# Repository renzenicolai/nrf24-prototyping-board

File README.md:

# nrf24-prototyping-board
Old project, uploaded just for you :-)

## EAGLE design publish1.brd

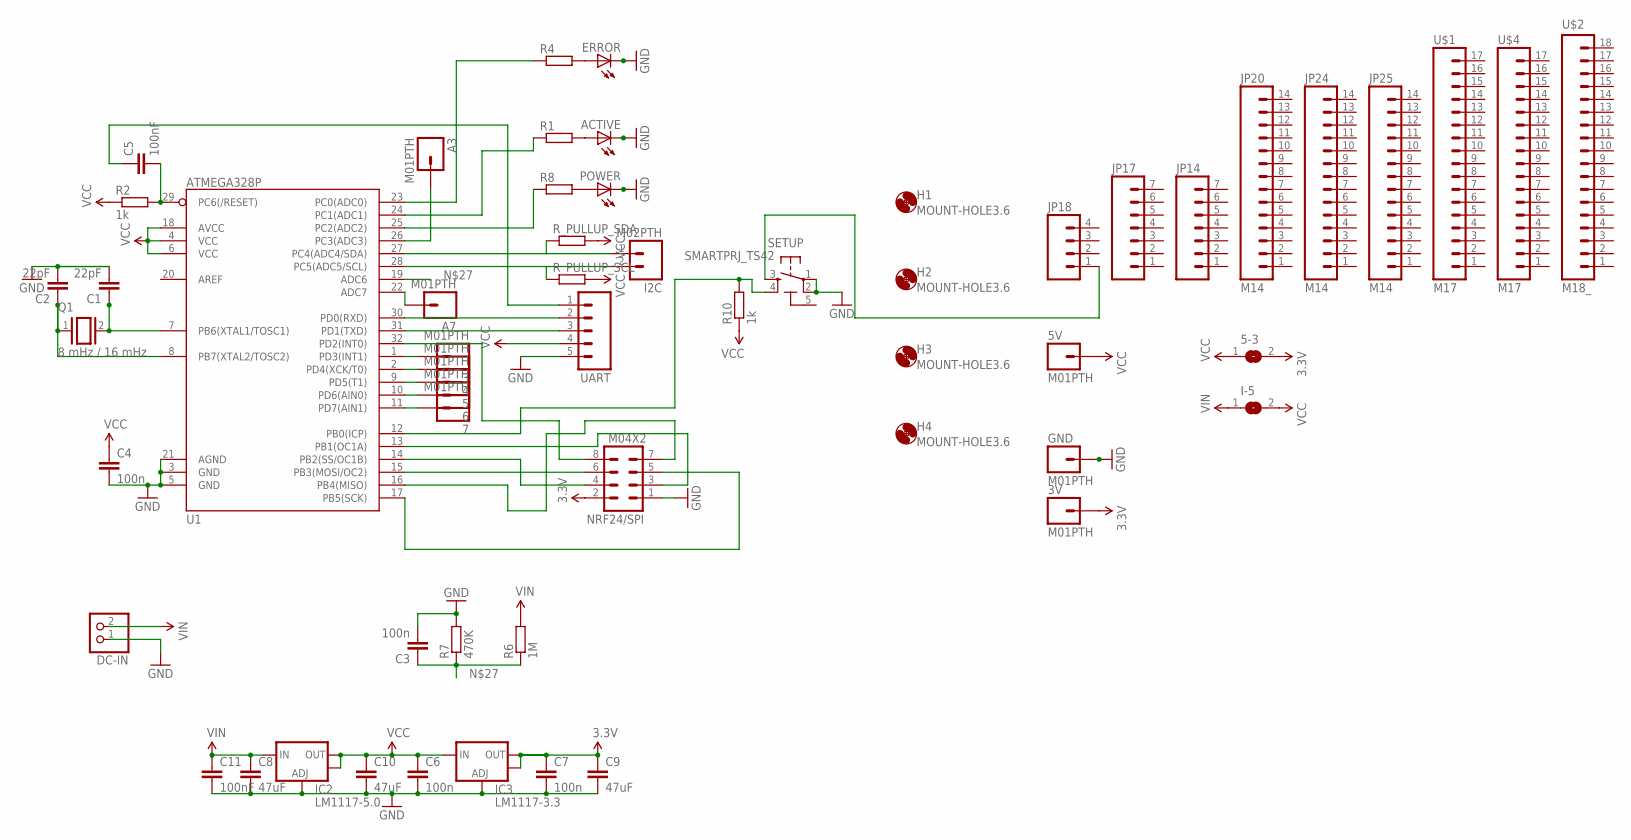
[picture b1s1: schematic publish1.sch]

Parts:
3, 3V, 4, 5, 5V, 6, 7: M01PTH; 1X01
5-3: JUMPER_SJ
A3, A7: M01PTH; 1X01
ACTIVE: LEDCHIP-LED0805; CHIP-LED0805
C1, C2: 22pF; C0805K
C3, C4, C6, C7: 100n; C0805K
C5, C11: 100nF; C0805K
C8, C9, C10: 47uF; 1210
DC-IN: PINHD-1X2; 1X02
ERROR: LEDCHIP-LED0805; CHIP-LED0805
GND: M01PTH; 1X01
H1, H2, H3, H4: MOUNT-HOLE3.6; 3,6
I2C: M02PTH; 1X02
I-5: JUMPER_SJ
IC2: LM1117-5.0; SOT223
IC3: LM1117-3.3; SOT223
JP14, JP17: M07; 1X07
JP18: M04PTH; 1X04
JP20, JP24, JP25: M14; 1X14
NRF24/SPI: M04X2; 2X4
POWER: LEDCHIP-LED0805; CHIP-LED0805
Q1: 8 mHz / 16 mHz; QS
R1, R4, R8: SMARTPRJ_R-EU_M0805; SMARTPRJ_M0805
R2, R10: 1k; SMARTPRJ_M0805
R6: 1M; SMARTPRJ_M0805
R7: 470K; SMARTPRJ_M0805
R_PULLUP_SCL: SMARTPRJ_R-EU_M0805; SMARTPRJ_M0805
R_PULLUP_SDA: SMARTPRJ_R-EU_M0805; SMARTPRJ_M0805
SETUP: SMARTPRJ_TS42
U1: ATMEGA328P; TQFP32-08
U$1, U$4: M17; 1X17
U$2: M18_; 1X18
UART: M05PTH; 1X05

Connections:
3.3V: 3V.1, 5-3.2, C7.1, C9.1, IC3.2 (OUT), IC3.4 (OUT), NRF24/SPI.2
5-GND: SETUP.5 (5-GND)
GND: ACTIVE.C, C1.2, C2.2, C3.2, C4.2, C6.2, C7.2, C8.2, C9.2, C10.2, C11.2, DC-IN.1, ERROR.C, GND.1, IC2.1 (ADJ), IC3.1 (ADJ), NRF24/SPI.1, POWER.C, R7.2, SETUP.1, SETUP.2, U1.3 (GND), U1.5 (GND), U1.21 (AGND), UART.5
unnamed: C1.1, Q1.2, U1.7 (PB6(XTAL1/TOSC1))
unnamed: C2.1, Q1.1, U1.8 (PB7(XTAL2/TOSC2))
unnamed: NRF24/SPI.3, U1.13 (PB1(OC1A))
unnamed: NRF24/SPI.4, U1.14 (PB2(SS/OC1B))
unnamed: NRF24/SPI.5, U1.17 (PB5(SCK))
unnamed: NRF24/SPI.7, U1.16 (PB4(MISO))
unnamed: C5.1, UART.1
unnamed: U1.30 (PD0(RXD)), UART.2
unnamed: U1.31 (PD1(TXD)), UART.3
unnamed: NRF24/SPI.6, U1.15 (PB3(MOSI/OC2))
unnamed: C5.2, R2.2, U1.29 (PC6(/RESET))
unnamed: NRF24/SPI.8, U1.32 (PD2(INT0))
unnamed: ACTIVE.A, R1.2
unnamed: ERROR.A, R4.2
unnamed: JP18.1, SETUP.3
unnamed: R4.1, U1.23 (PC0(ADC0))
unnamed: R1.1, U1.24 (PC1(ADC1))
unnamed: C3.1, R6.1, R7.1, U1.19 (ADC6)
unnamed: POWER.A, R8.2
unnamed: R8.1, U1.25 (PC2(ADC2))
unnamed: A3.1, U1.26 (PC3(ADC3))
unnamed: 3.1, U1.1 (PD3(INT1))
unnamed: 4.1, U1.2 (PD4(XCK/T0))
unnamed: 5.1, U1.9 (PD5(T1))
unnamed: 6.1, U1.10 (PD6(AIN0))
unnamed: 7.1, U1.11 (PD7(AIN1))
unnamed: A7.1, U1.22 (ADC7)
unnamed: R10.2, SETUP.4, U1.12 (PB0(ICP))
SCL: I2C.2, R_PULLUP_SCL.1, U1.28 (PC5(ADC5/SCL))
SDA: I2C.1, R_PULLUP_SDA.1, U1.27 (PC4(ADC4/SDA))
VCC: 5-3.1, 5V.1, C4.1, C6.1, C10.1, I-5.2, IC2.2 (OUT), IC2.4 (OUT), IC3.3 (IN), R2.1, R10.1, R_PULLUP_SCL.2, R_PULLUP_SDA.2, U1.4 (VCC), U1.6 (VCC), U1.18 (AVCC), UART.4
VIN: C8.1, C11.1, DC-IN.2, I-5.1, IC2.3 (IN), R6.2

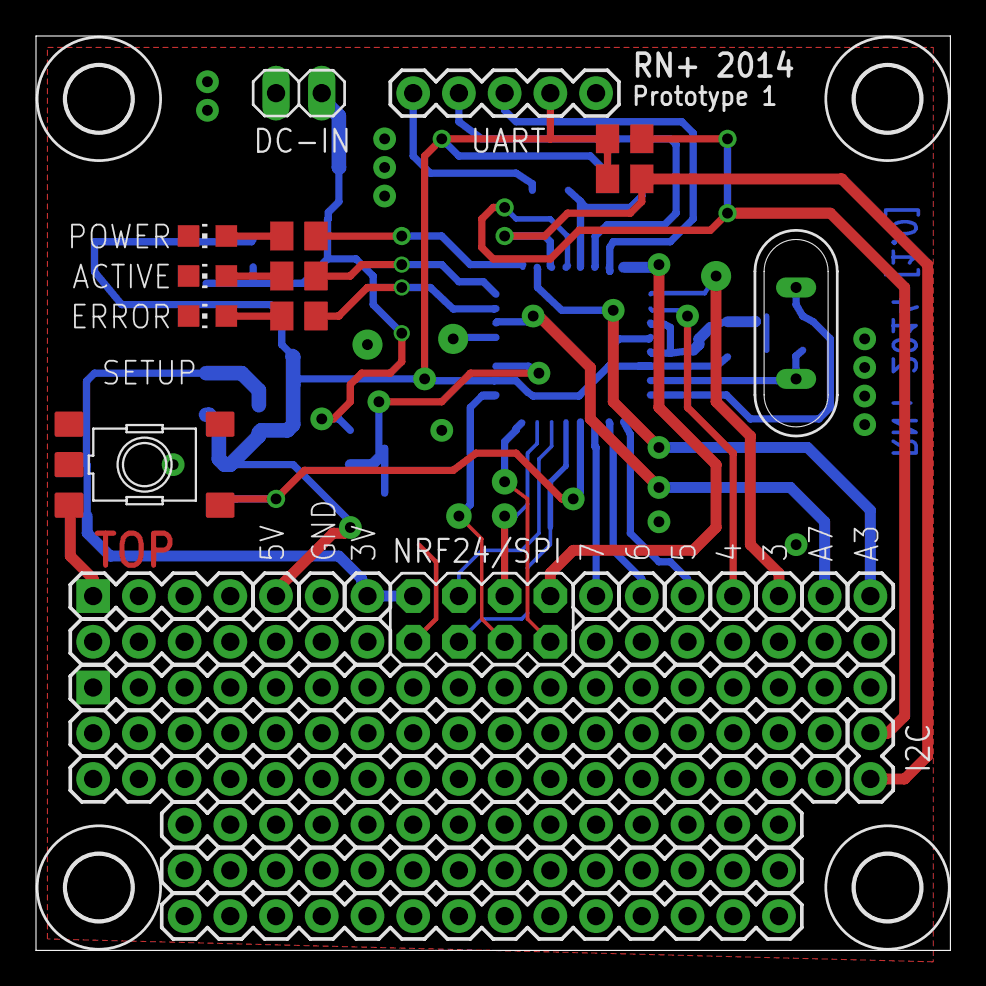
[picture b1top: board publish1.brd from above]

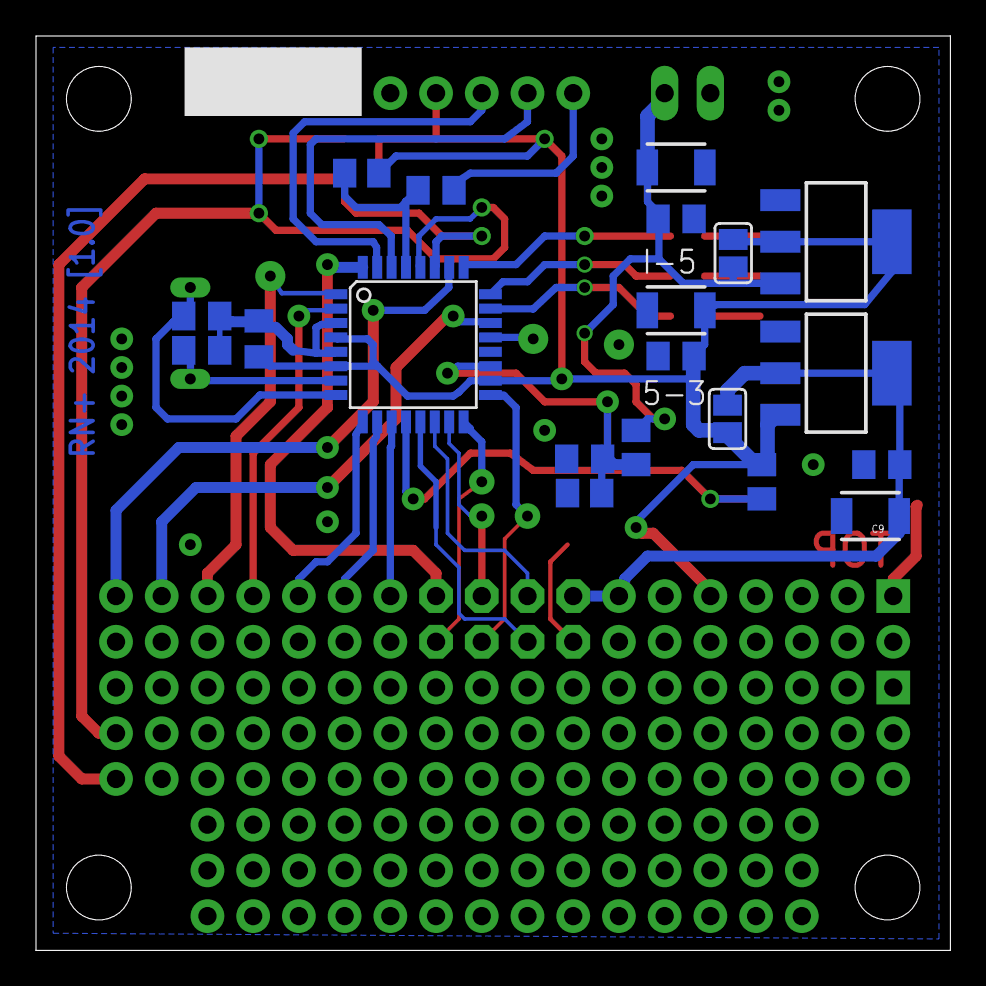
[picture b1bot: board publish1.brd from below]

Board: 2 copper layers, 50.8 x 50.8 mm, 57 parts (20 on the bottom side), 34 nets.

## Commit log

2016-02-18 Added files via upload

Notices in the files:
parts and their libraries:
SparkFun-DigitalIC: Licensing: Creative Commons ShareAlike 4.0 International - https://creativecommons.org/licenses/by-sa/4.0
